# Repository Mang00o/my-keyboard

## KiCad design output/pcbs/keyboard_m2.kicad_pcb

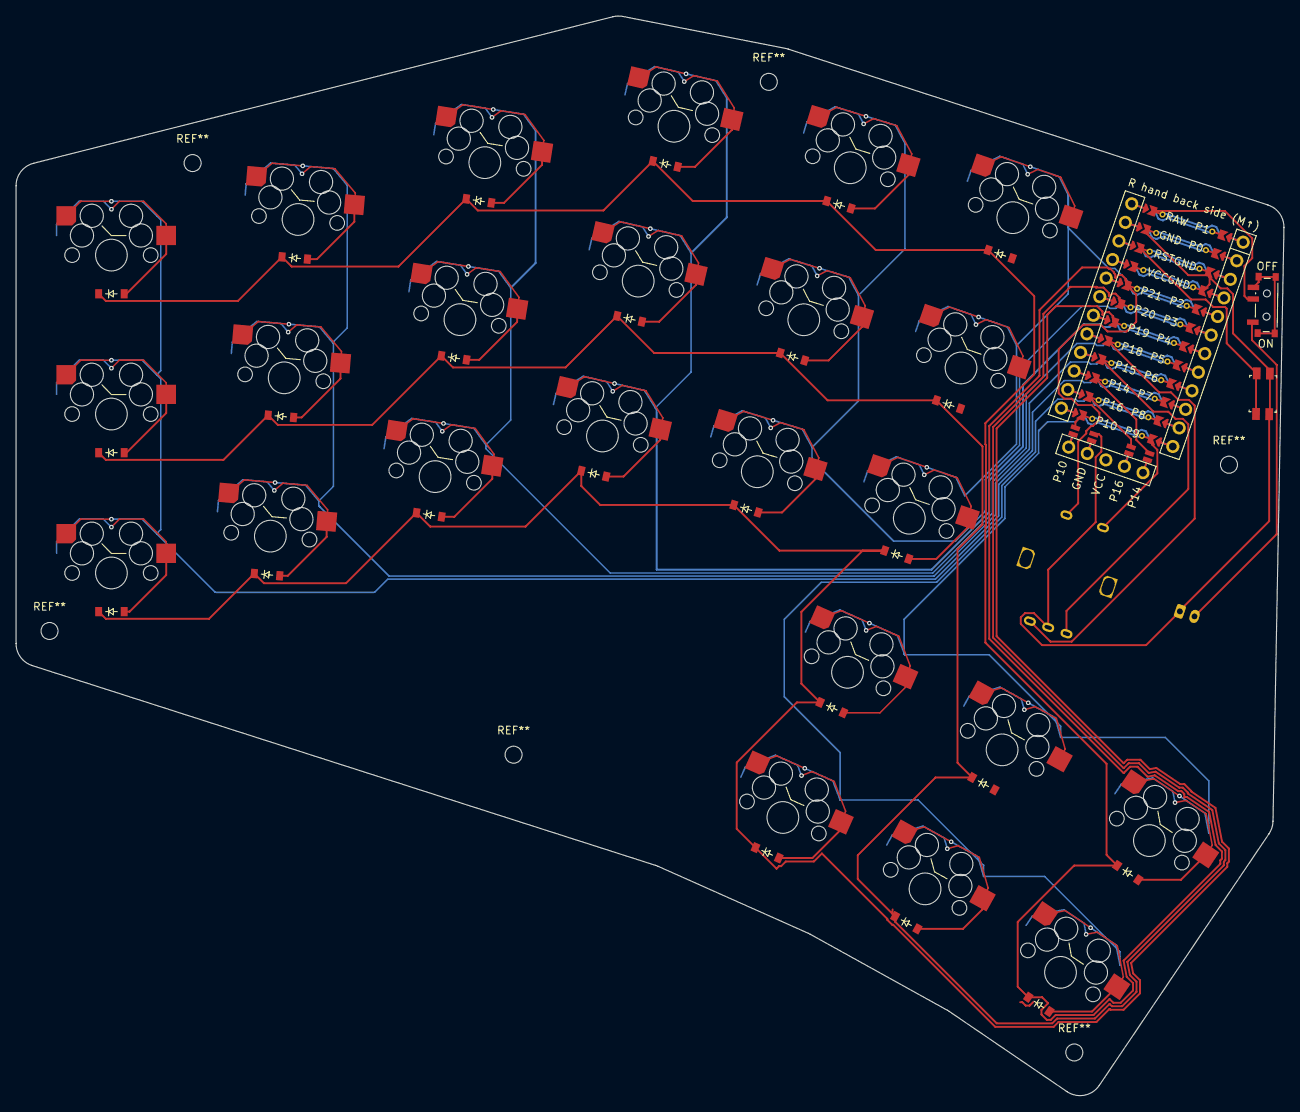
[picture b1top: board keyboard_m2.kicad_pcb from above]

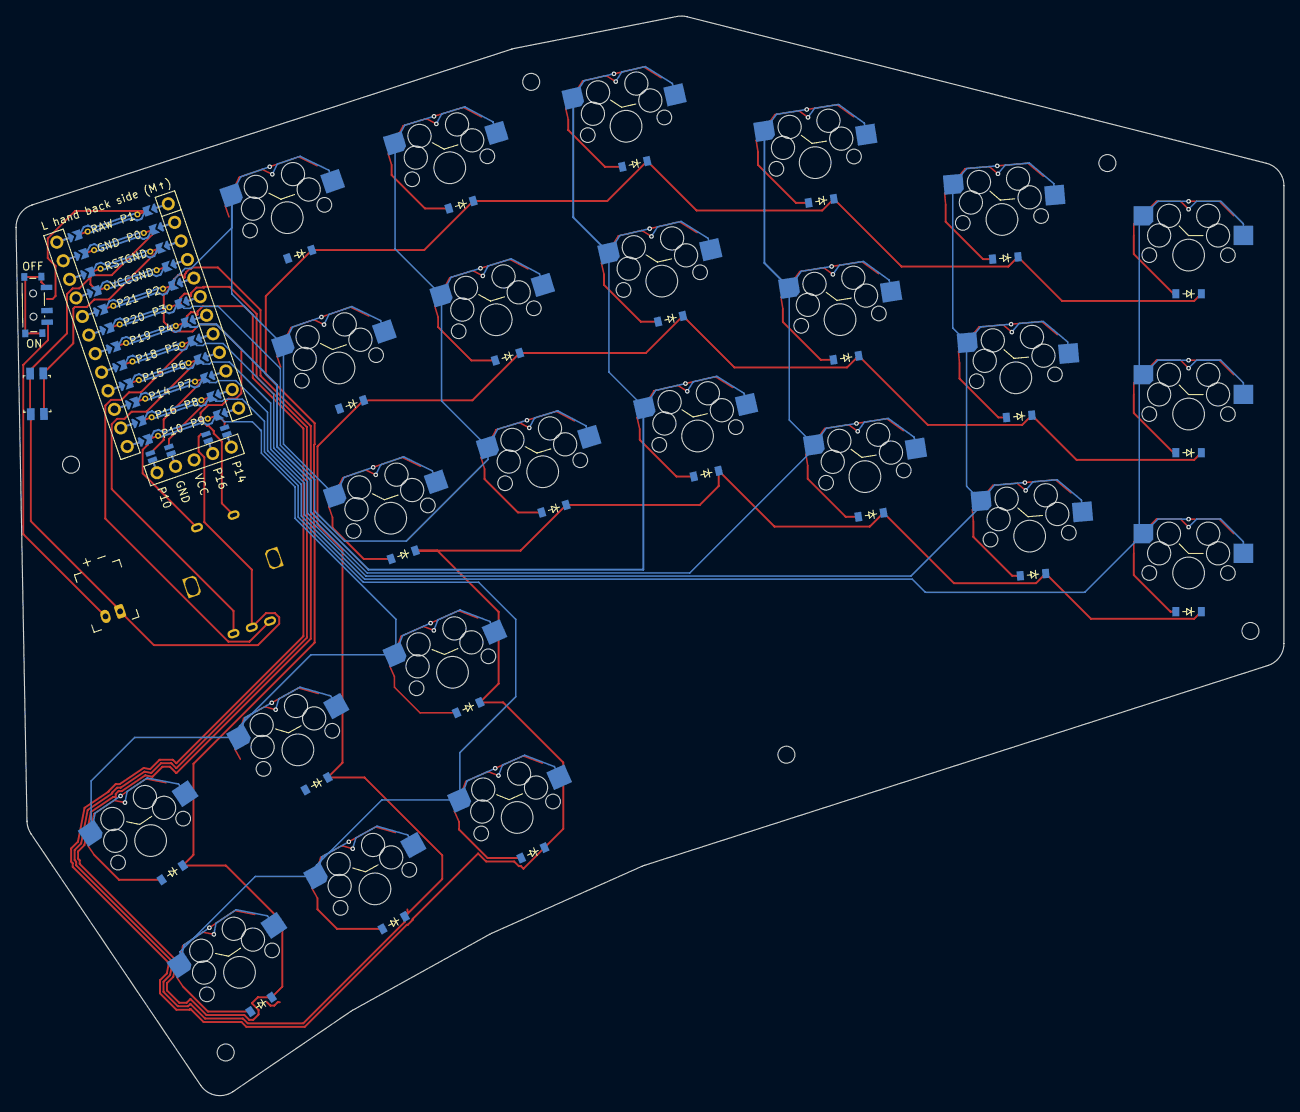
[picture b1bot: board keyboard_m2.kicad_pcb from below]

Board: 2 copper layers, 163.9 x 139.6 mm, 54 parts (25 on the bottom side), 45 nets.

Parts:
D1, D2, D3, D4, D5, D6, D7, D8, D9, D10, D11, D12, D13, D14, D15, D16, D17, D18, D19, D20, D21, D22, D23, D24: diode_tht_sod123
DISP1: display_nice_view
JST1: battery_connector_jst_ph_2
MCU1: mcu_nice_nano
PWR1: power_switch_smd_side
RE1: rotary_encoder_ec11_ec12
RST1: reset_switch_smd_side
S1, S2, S3, S4, S5, S6, S7, S8, S9, S10, S11, S12, S13, S14, S15, S16, S17, S18, S19, S20, S21, S22, S23, S24: switch_mx

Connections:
BAT_P: JST1.2, PWR1.1, PWR1.3
DISP1_1: DISP1.1, DISP1.10, DISP1.23
DISP1_2: DISP1.2, DISP1.11, DISP1.22
DISP1_4: DISP1.4, DISP1.12, DISP1.21
DISP1_5: DISP1.5, DISP1.13, DISP1.20
GND: DISP1.15, DISP1.25, JST1.1, MCU1.103, MCU1.104, MCU1.123, RE1.B, RST1.1, RST1.3
P2: MCU1.105, S16.2, S17.2, S18.2
P3: MCU1.106, S13.2, S14.2, S15.2
P4: MCU1.107, S10.2, S11.2, S12.2
P5: MCU1.108, S7.2, S8.2, S9.2
P6: MCU1.109, S4.2, S5.2, S6.2
P7: MCU1.110, S1.2, S2.2, S3.2
P8: MCU1.111, S19.2, S21.2, S23.2
P9: MCU1.112, RE1.S2, S20.2, S22.2, S24.2
P10: DISP1.14, DISP1.24, MCU1.113
P14: DISP1.17, DISP1.27, MCU1.115
P15: MCU1.116, RE1.A
P16: DISP1.16, DISP1.26, MCU1.114
P18: MCU1.117, RE1.C
P19: D1.1, D4.1, D7.1, D10.1, D13.1, D16.1, D19.1, D20.1, MCU1.118
P20: D2.1, D5.1, D8.1, D11.1, D14.1, D17.1, D21.1, D22.1, MCU1.119
P21: D3.1, D6.1, D9.1, D12.1, D15.1, D18.1, D23.1, D24.1, MCU1.120, RE1.S1
RAW: MCU1.124, PWR1.2
RST: MCU1.122, RST1.2, RST1.4
VCC: DISP1.3, MCU1.121
center_bottom: D22.2, S22.1
center_top: D21.2, S21.1
index_bottom: D13.2, S13.1
index_middle: D14.2, S14.1
index_top: D15.2, S15.1
left_bottom: D1.2, D20.2, S1.1, S20.1
left_middle: D2.2, S2.1
left_top: D3.2, D19.2, S3.1, S19.1
middle_bottom: D10.2, S10.1
middle_middle: D11.2, S11.1
middle_top: D12.2, S12.1
pinkie_bottom: D4.2, S4.1
pinkie_middle: D5.2, S5.1
pinkie_top: D6.2, S6.1
right_bottom: D16.2, D24.2, S16.1, S24.1
right_middle: D17.2, S17.1
right_top: D18.2, D23.2, S18.1, S23.1
ring_bottom: D7.2, S7.1
ring_middle: D8.2, S8.1
ring_top: D9.2, S9.1

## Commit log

2025-11-05 correct orientation of microcontroller
2025-12-01 add nice!view
2025-12-01 easier version
2025-12-05 Correct easy pcb
2025-12-05 Correzioni pin
2025-12-11 correct connections
2025-12-11 better pinning
2025-12-12 mapped reversible nice!view
2025-12-12 mapped rotary encoder
2025-12-15 oriente power and reset buttons
2025-12-15 Add cases
2025-12-16 add outputs
